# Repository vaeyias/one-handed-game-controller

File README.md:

![Offical github repo (PCBs are here)] https://github.com/MIT-Assistive-Technology/one-handed-game-controller
# :video_game: **One-Handed Game Controller (Left-Handed)**

## 🛠️ **Tools and Materials**
- 3D Printer
- Soldering Kit
- 1 Arduino Micro 
- 2 Thumb Joysticks (KY-023)
- 16 Two-Pin Buttons
- Electrical Wire Cables
- PLA
- 1 ¾ in machine screws size 2-56
- (optional) Foam tape

## :memo: **Instructions**
1. Download ___ files
2. 3D print ___ files
4. Print PCB
5. Solder
6. Upload code to the Arduino
7. Assemble
8. TO DO

## :mag_right: Problem Statement
**Modern game controllers do not accommodate for one-handed users.**

After a stroke or injury, a person may lose some function in their body. Recreational products for the public are often made with the assumption that a person has full control of their body, which means that after permanent injuries, a person may become limited in their choice of hobbies.

Our codesigner, Susan Bibbins, suffers from chronic pain from fibromyalgia and has limited function in her right hand. She always wanted to play video games; however, modern controllers do not accomodate one-handed users.

Our team aims to develop a comfortable and accessible game controller designed specifically for one-handed users so that our codesigner can finally play video games that she has always wanted to try.

## 🔗 References

## ✍️ Acknowledgements
To be completed

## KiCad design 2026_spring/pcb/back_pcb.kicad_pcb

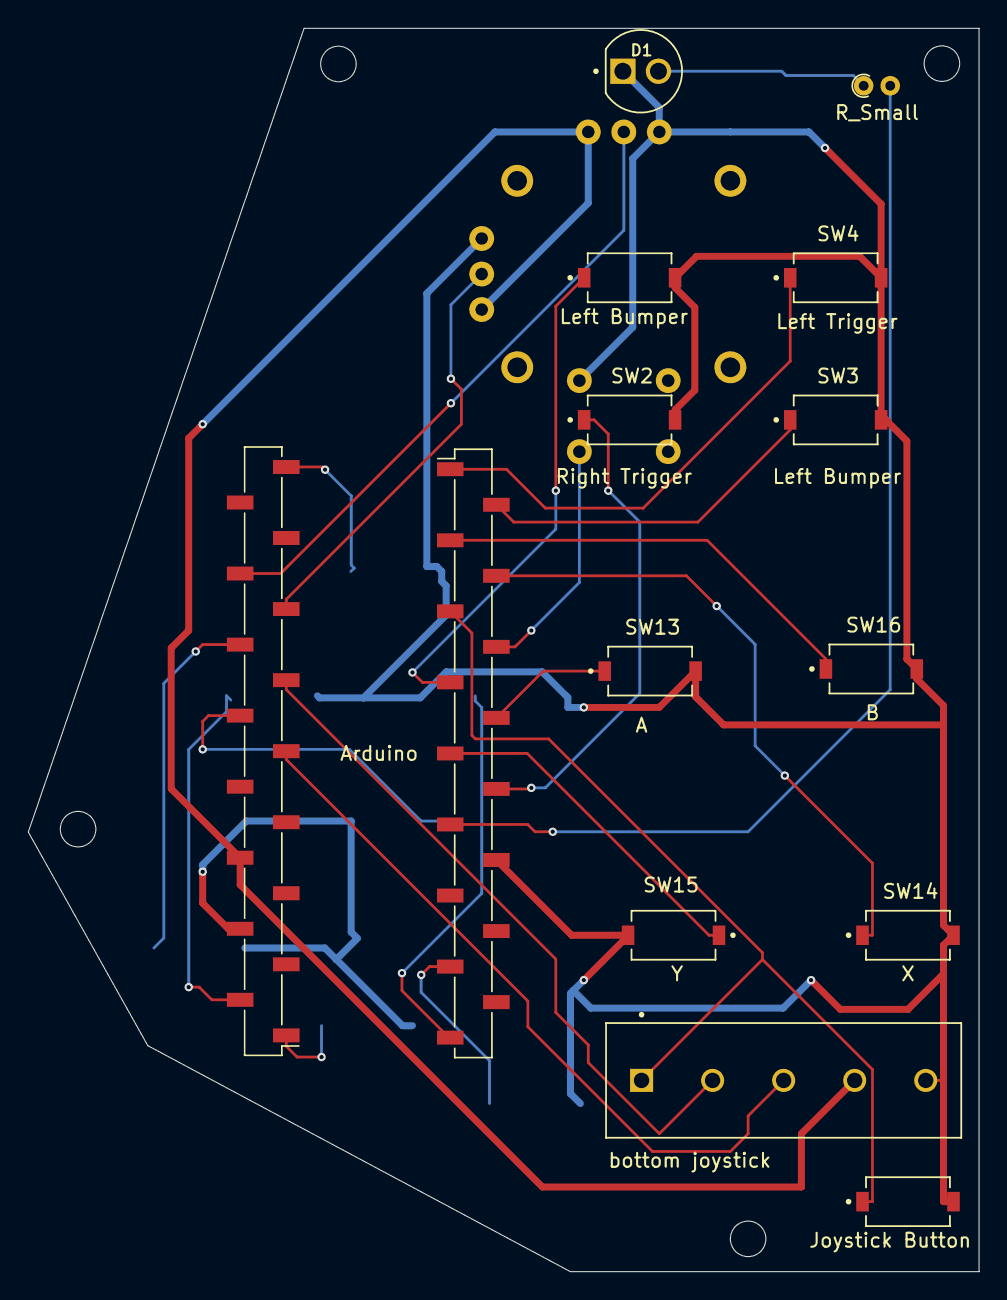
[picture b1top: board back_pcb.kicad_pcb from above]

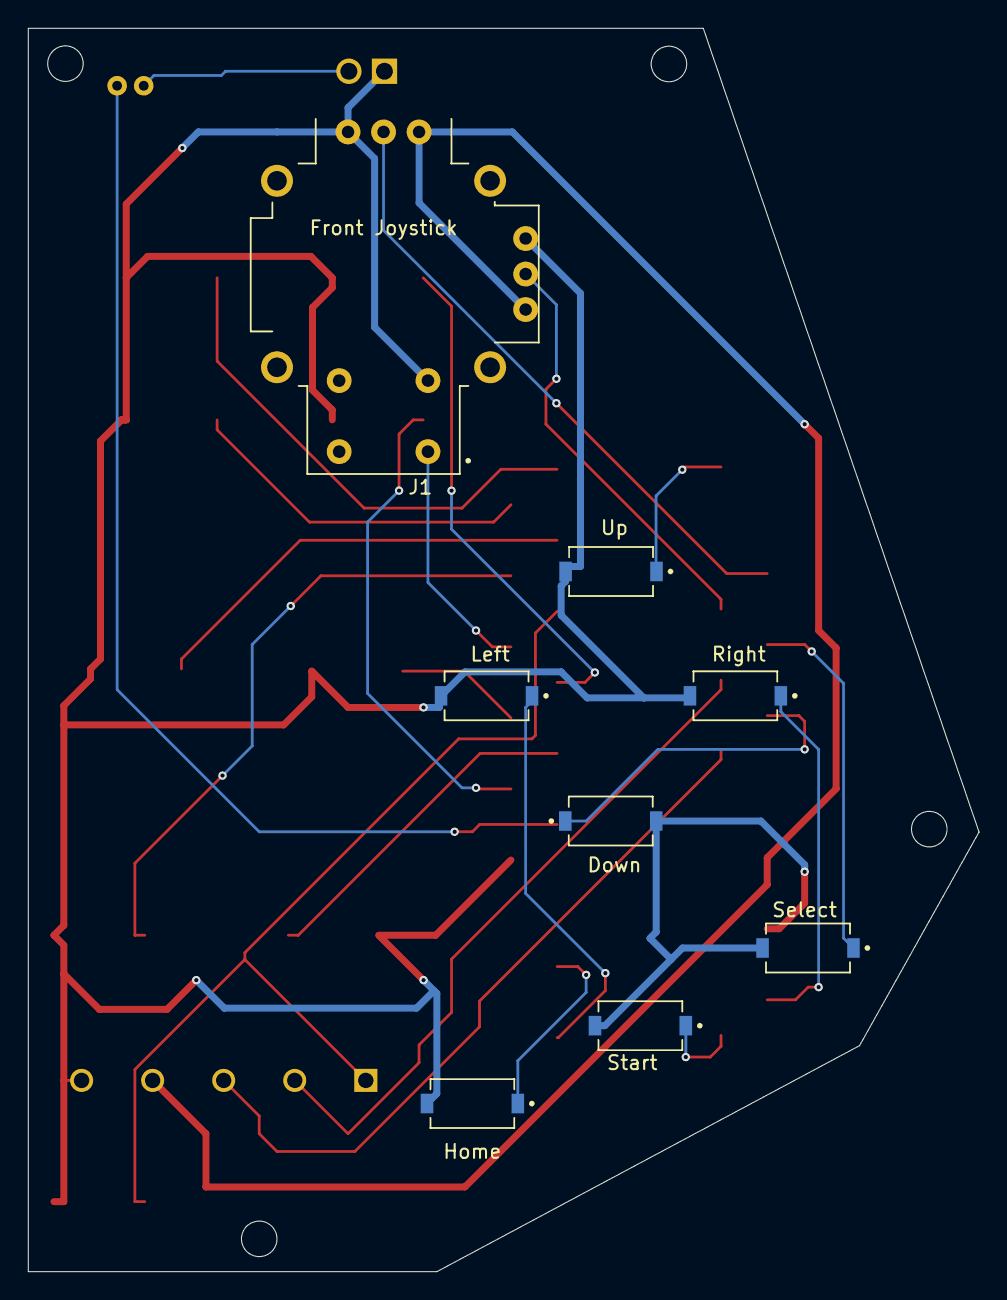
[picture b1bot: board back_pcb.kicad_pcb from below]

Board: 2 copper layers, 68.0 x 88.9 mm, 22 parts (8 on the bottom side), 27 nets.

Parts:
D1: LED; LEDRD254W57D500H1070
J1: Front Joystick; XDCR_COM-09032
J2: bottom joystick; TE_282837-5
J3, J4: Arduino; PinSocket_1x17_P2.54mm_Vertical_SMD_Pin1Left
R1: R_Small; R_Axial_DIN0204_L3.6mm_D1.6mm_P1.90mm_Vertical
SW1: Left Trigger; SW_PTS636_SM43J_SMTR_LFS
SW2: Right Trigger; SW_PTS636_SM43J_SMTR_LFS
SW3, SW4: Left Bumper; SW_PTS636_SM43J_SMTR_LFS
SW5: Up; SW_PTS636_SM43J_SMTR_LFS
SW6: Down; SW_PTS636_SM43J_SMTR_LFS
SW8: Right; SW_PTS636_SM43J_SMTR_LFS
SW9: Left; SW_PTS636_SM43J_SMTR_LFS
SW10: Home; SW_PTS636_SM43J_SMTR_LFS
SW11: Start; SW_PTS636_SM43J_SMTR_LFS
SW13: A; SW_PTS636_SM43J_SMTR_LFS
SW14: X; SW_PTS636_SM43J_SMTR_LFS
SW15: Y; SW_PTS636_SM43J_SMTR_LFS
SW16: B; SW_PTS636_SM43J_SMTR_LFS
SW17: Select; SW_PTS636_SM43J_SMTR_LFS
joy_SW: Joystick Button; SW_PTS636_SM43J_SMTR_LFS

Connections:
/A0: J1.H2, J4.14
/A1: J1.V2, J4.13
/A2: J4.12, SW17.1
/A3: J2.2, J4.11
/A4: J4.10, SW6.1
/A5: J2.3, J4.9
/D1: J3.15, SW10.1
/D2: J3.11, R1.2
/D3: J3.10, SW2.1
/D4: J3.9, SW15.1
/D5: J3.8, SW13.1
/D6: J3.7, SW1.1
/D7: J1.B1A, J3.6
/D8: J2.1, J3.5, joy_SW.1
/D9: J3.4, SW14.1
/D10: J3.3, SW16.1
/D11: J3.2, SW3.1
/D12: J3.1, SW4.1
/D13: J4.17, SW5.1
/D14: J4.2, SW8.1
/D15: J4.1, SW11.1
/D16: J3.17, SW9.1
/GND: D1.GND, J1.B2A, J1.H3, J1.V3, J2.5, J3.12, J4.4, SW1.2, SW2.2, SW3.2, SW4.2, SW5.2, SW6.2, SW8.2, SW9.2, SW10.2, SW11.2, SW13.2, SW14.2, SW15.2, SW16.2, SW17.2, joy_SW.2
/NC: J4.7, J4.8
/R1: D1.R1, R1.1
/RST: J3.13, J4.5
/VCC: J1.H1, J1.V1, J2.4, J4.6

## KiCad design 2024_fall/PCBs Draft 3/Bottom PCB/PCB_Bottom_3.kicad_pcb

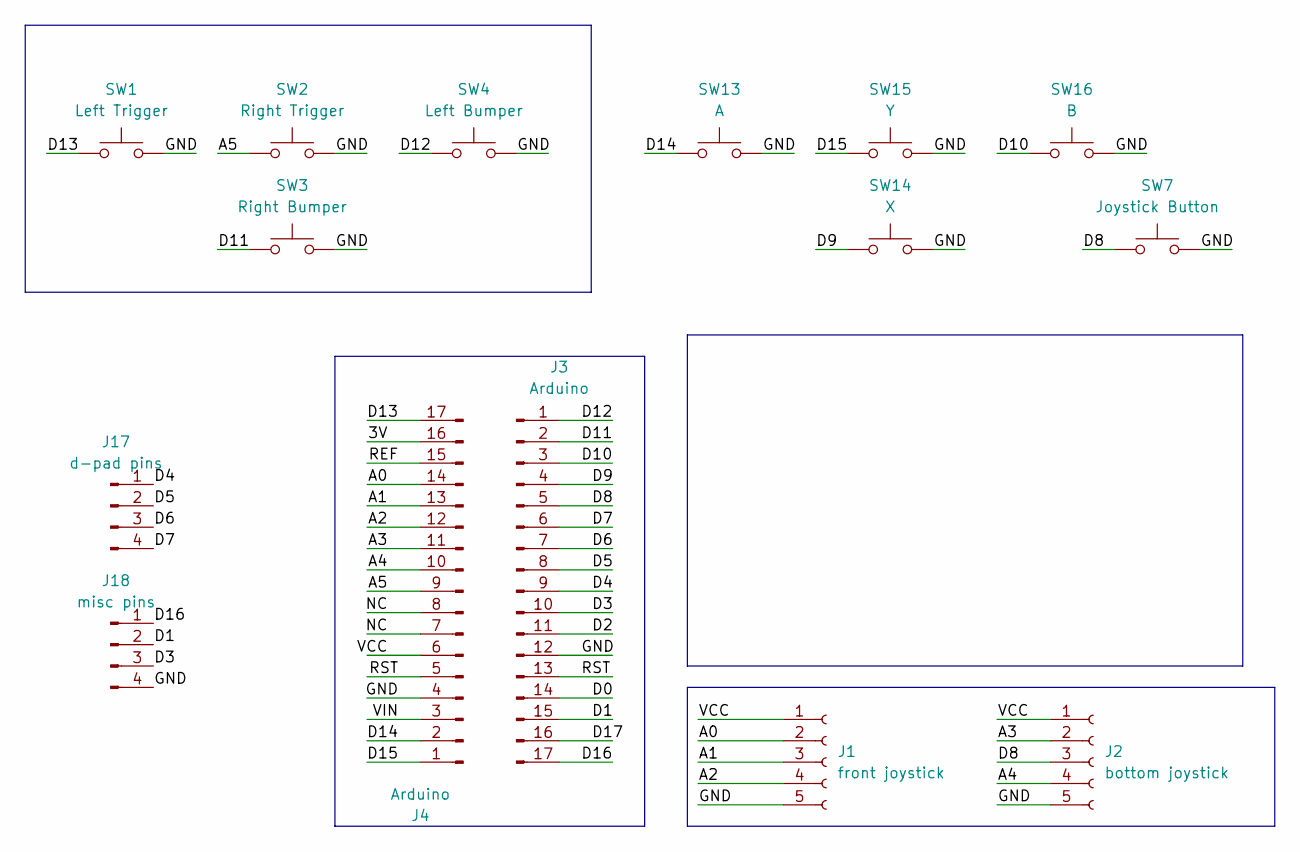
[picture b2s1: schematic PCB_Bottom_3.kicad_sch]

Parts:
J1: front joystick; PinSocket_1x05_P2.54mm_Vertical
J2: bottom joystick; PinSocket_1x05_P2.54mm_Vertical
J3, J4: Arduino; PinSocket_1x17_P2.54mm_Vertical
J17: d-pad pins; PinSocket_1x04_P2.54mm_Vertical
J18: misc pins; PinSocket_1x04_P2.54mm_Vertical
SW1: Left Trigger; SW_BUTT-2
SW2: Right Trigger; SW_BUTT-2
SW3: Right Bumper; SW_BUTT-2
SW4: Left Bumper; SW_BUTT-2
SW7: Joystick Button; SW_BUTT-2
SW13: A; SW_BUTT-2
SW14: X; SW_BUTT-2
SW15: Y; SW_BUTT-2
SW16: B; SW_BUTT-2

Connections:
/3V: J4.16
/A0: J1.2, J4.14
/A1: J1.3, J4.13
/A2: J1.4, J4.12
/A3: J2.2, J4.11
/A4: J2.4, J4.10
/A5: J4.9, SW2.1
/D0: J3.14
/D1: J3.15, J18.2
/D2: J3.11
/D3: J3.10, J18.3
/D4: J3.9, J17.1
/D5: J3.8, J17.2
/D6: J3.7, J17.3
/D7: J3.6, J17.4
/D8: J2.3, J3.5, SW7.1
/D9: J3.4, SW14.1
/D10: J3.3, SW16.1
/D11: J3.2, SW3.1
/D12: J3.1, SW4.1
/D13: J4.17, SW1.1
/D14: J4.2, SW13.1
/D15: J4.1, SW15.1
/D16: J3.17, J18.1
/D17: J3.16
/GND: J1.5, J2.5, J3.12, J4.4, J18.4, SW1.2, SW2.2, SW3.2, SW4.2, SW7.2, SW13.2, SW14.2, SW15.2, SW16.2
/NC: J4.7, J4.8
/REF: J4.15
/RST: J3.13, J4.5
/VCC: J1.1, J2.1, J4.6
/VIN: J4.3

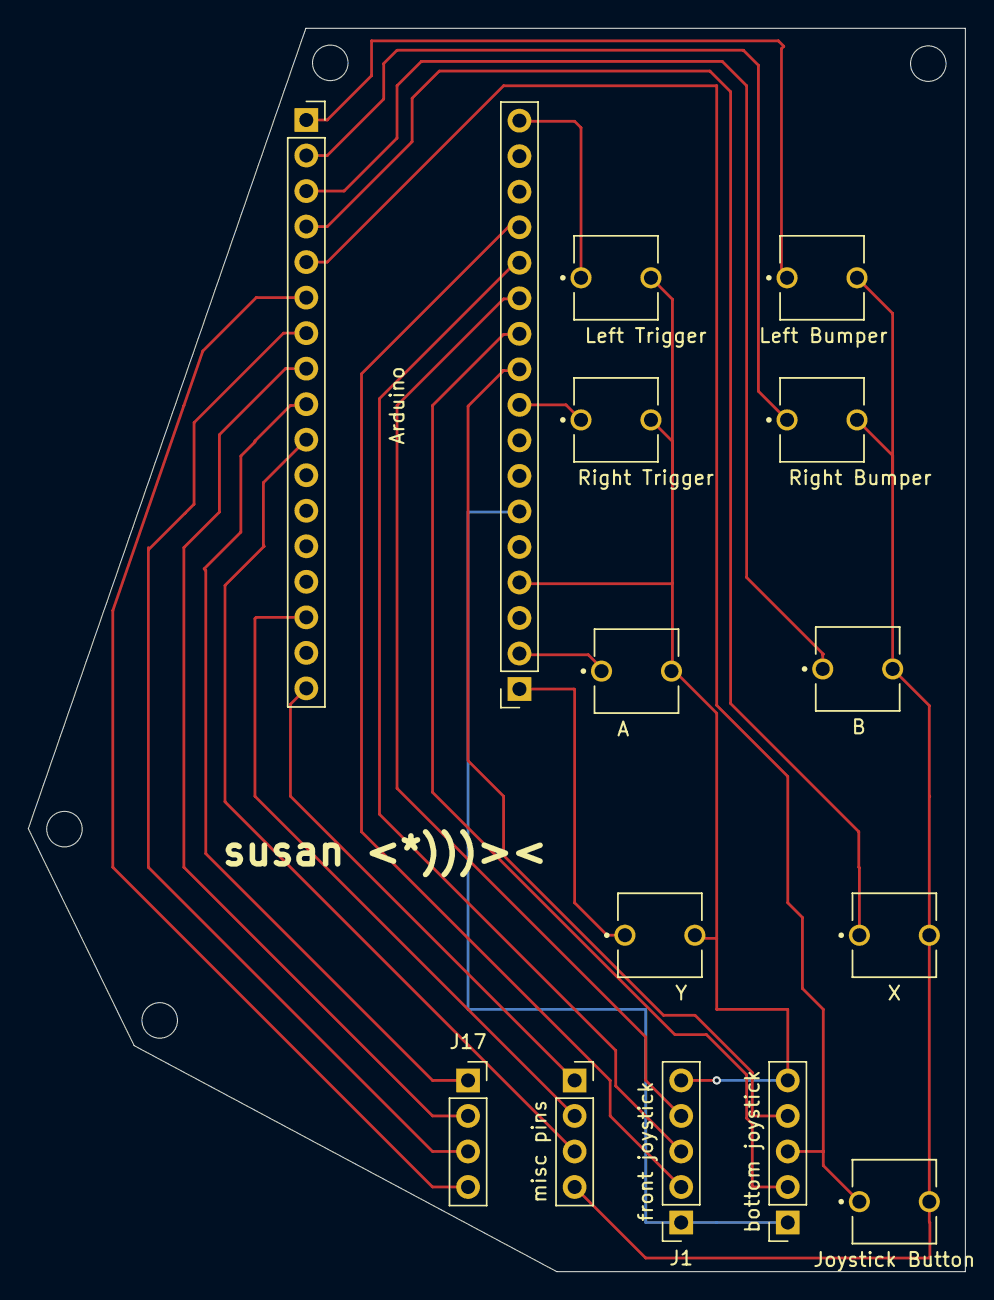
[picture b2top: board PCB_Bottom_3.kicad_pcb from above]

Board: 2 copper layers, 67.0 x 88.9 mm, 15 parts (0 on the bottom side), 25 nets.

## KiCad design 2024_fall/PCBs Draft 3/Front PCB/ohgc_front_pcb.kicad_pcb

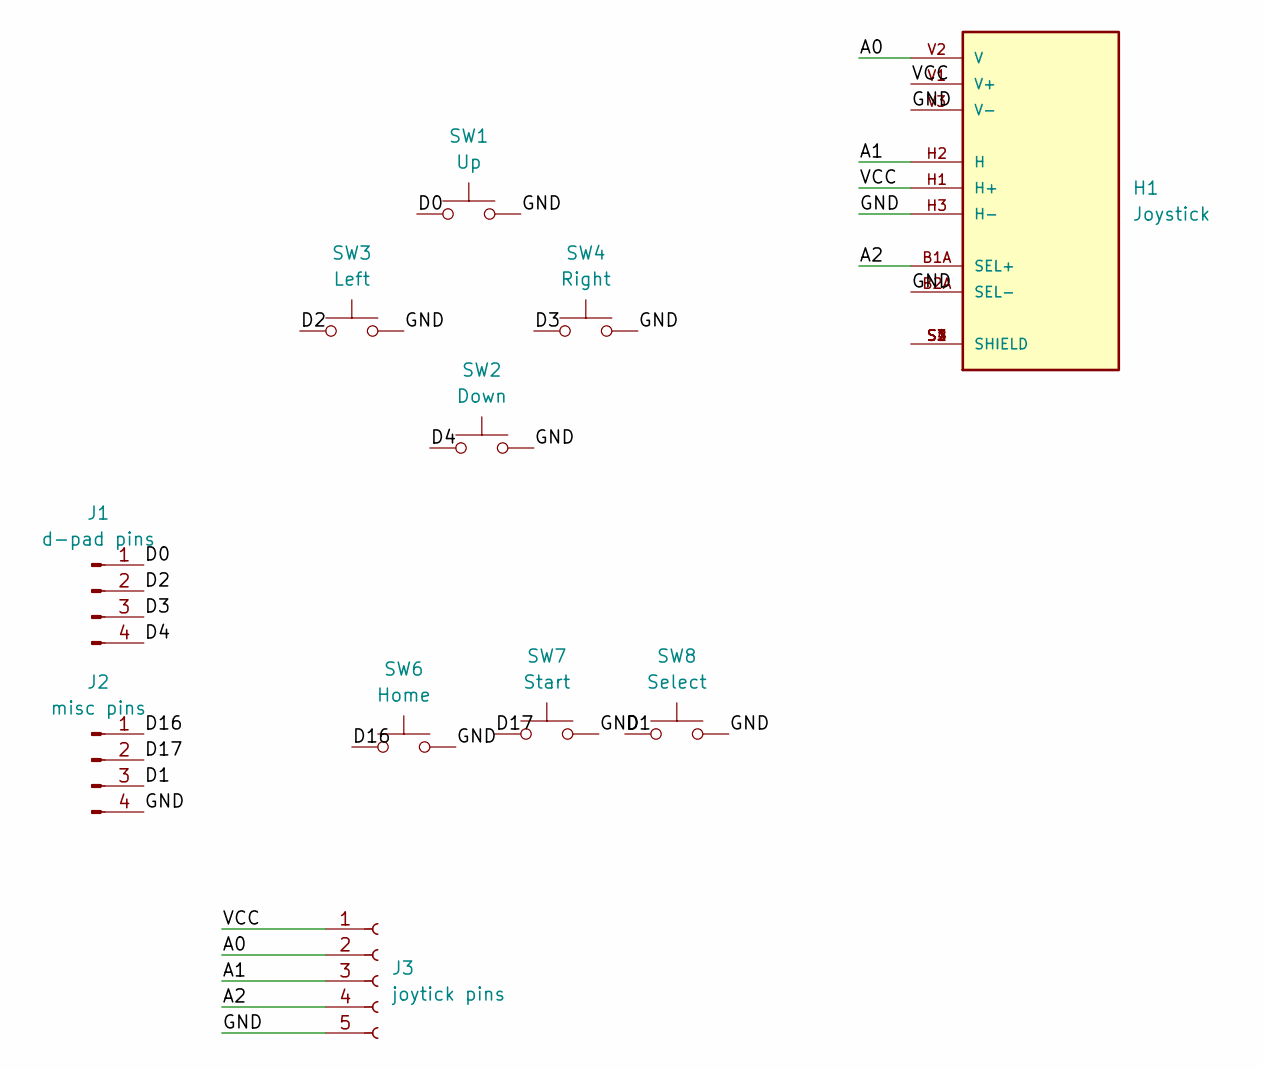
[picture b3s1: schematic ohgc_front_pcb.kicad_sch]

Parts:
H1: Joystick; XDCR_COM-09032; PARTREV N/A
J1: d-pad pins; PinSocket_1x04_P2.54mm_Vertical
J2: misc pins; PinSocket_1x04_P2.54mm_Vertical
J3: joytick pins; PinSocket_1x05_P2.54mm_Vertical
SW1: Up; SW_BUTT-2
SW2: Down; SW_BUTT-2
SW3: Left; SW_BUTT-2
SW4: Right; SW_BUTT-2
SW6: Home; SW_BUTT-2
SW7: Start; SW_BUTT-2
SW8: Select; SW_BUTT-2

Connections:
/A0: H1.V2 (V), J3.2
/A1: H1.H2 (H), J3.3
/A2: H1.B1A (SEL+), J3.4
/D0: J1.1, SW1.1
/D1: J2.3, SW8.1
/D2: J1.2, SW3.1
/D3: J1.3, SW4.1
/D4: J1.4, SW2.1
/D16: J2.1, SW6.1
/D17: J2.2, SW7.1
/GND: H1.B2A (SEL-), H1.H3 (H-), H1.V3 (V-), J2.4, J3.5, SW1.2, SW2.2, SW3.2, SW4.2, SW6.2, SW7.2, SW8.2
/VCC: H1.H1 (H+), H1.V1 (V+), J3.1
unnamed: H1.S1 (SHIELD), H1.S2 (SHIELD), H1.S3 (SHIELD), H1.S4 (SHIELD)

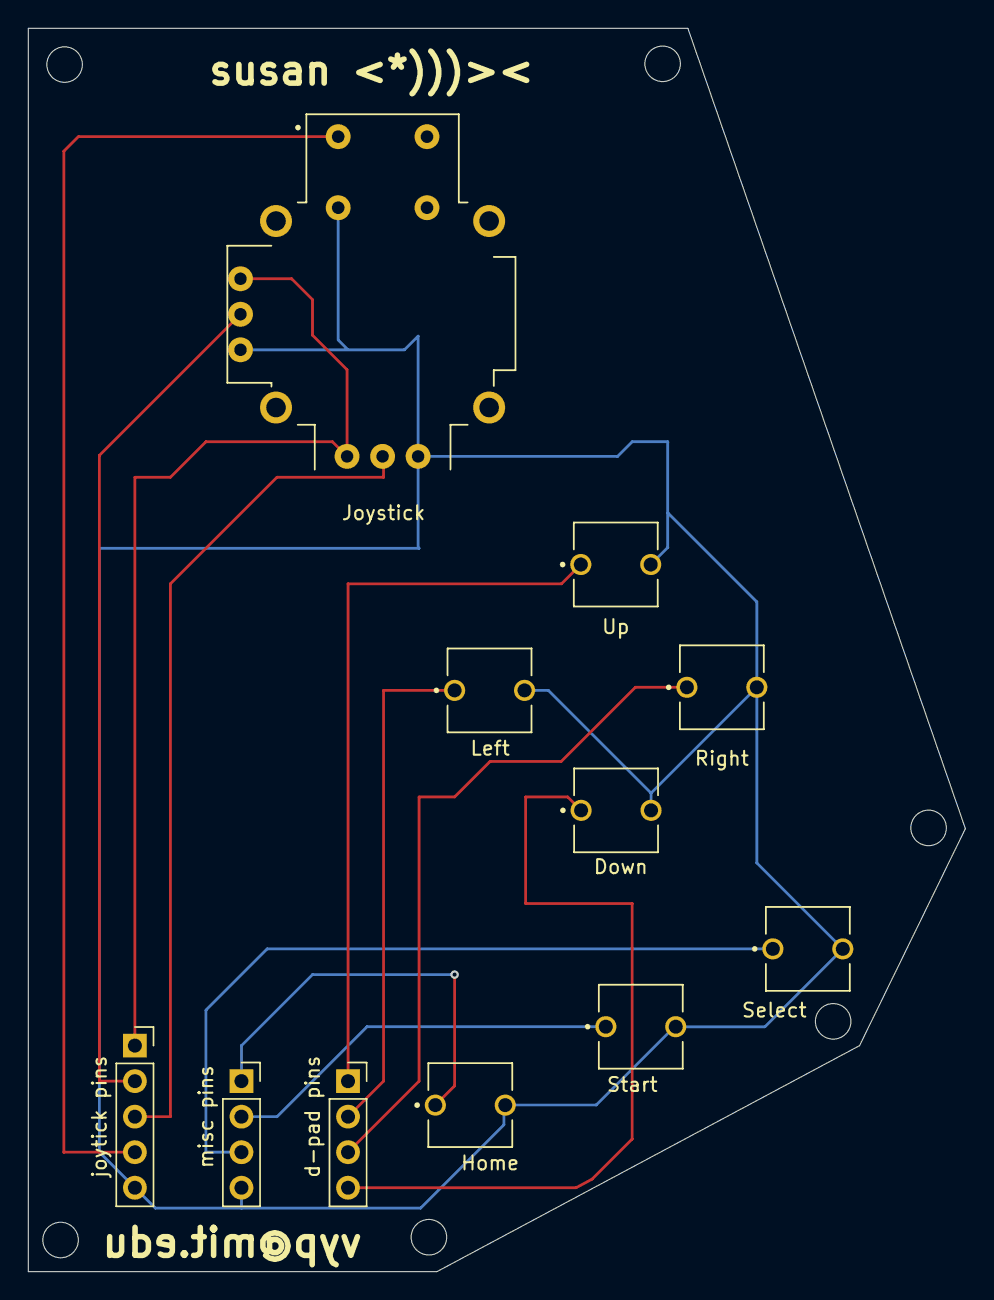
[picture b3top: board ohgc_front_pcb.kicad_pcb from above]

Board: 2 copper layers, 67.0 x 88.9 mm, 11 parts (0 on the bottom side), 13 nets.

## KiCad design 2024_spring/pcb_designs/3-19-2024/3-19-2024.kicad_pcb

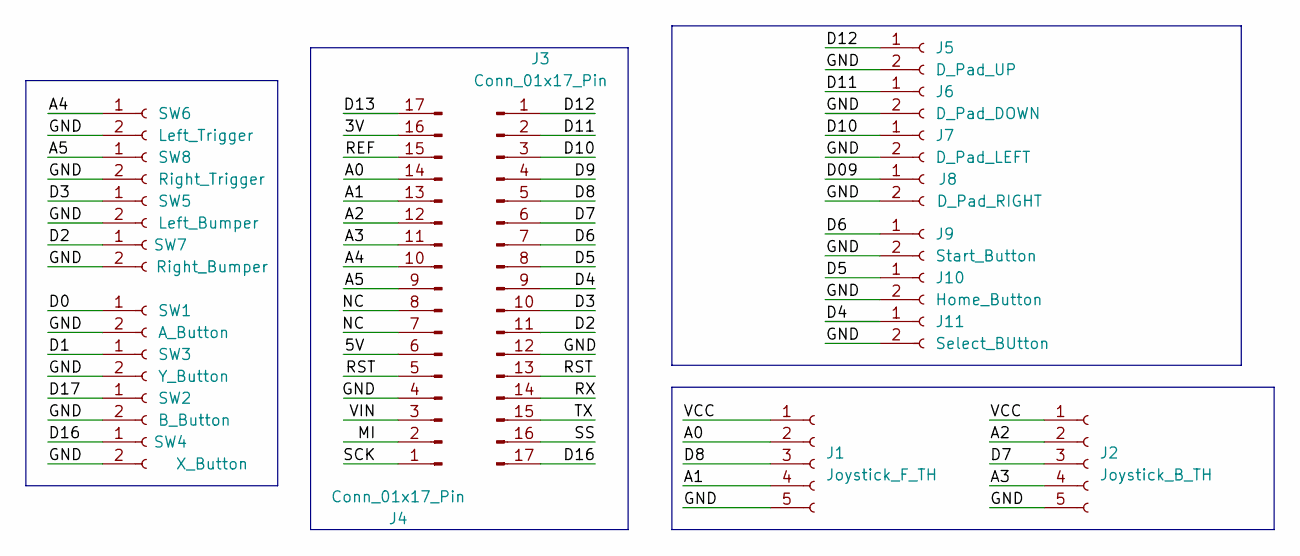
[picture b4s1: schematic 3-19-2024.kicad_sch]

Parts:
J1: Joystick_F_TH; SolderWire-0.1sqmm_1x05_P3.6mm_D0.4mm_OD1mm
J2: Joystick_B_TH; SolderWire-0.1sqmm_1x05_P3.6mm_D0.4mm_OD1mm
J3, J4: Conn_01x17_Pin; PinSocket_1x17_P2.54mm_Vertical
J5: D_Pad_UP; SolderWire-0.1sqmm_1x02_P3.6mm_D0.4mm_OD1mm
J6: D_Pad_DOWN; SolderWire-0.1sqmm_1x02_P3.6mm_D0.4mm_OD1mm
J7: D_Pad_LEFT; SolderWire-0.1sqmm_1x02_P3.6mm_D0.4mm_OD1mm
J8: D_Pad_RIGHT; SolderWire-0.1sqmm_1x02_P3.6mm_D0.4mm_OD1mm
J9: Start_Button; SolderWire-0.1sqmm_1x02_P3.6mm_D0.4mm_OD1mm
J10: Home_Button; SolderWire-0.1sqmm_1x02_P3.6mm_D0.4mm_OD1mm
J11: Select_BUtton; SolderWire-0.1sqmm_1x02_P3.6mm_D0.4mm_OD1mm
SW1: A_Button; SolderWire-0.1sqmm_1x02_P3.6mm_D0.4mm_OD1mm
SW2: B_Button; SolderWire-0.1sqmm_1x02_P3.6mm_D0.4mm_OD1mm
SW3: Y_Button; SolderWire-0.1sqmm_1x02_P3.6mm_D0.4mm_OD1mm
SW4: X_Button; SolderWire-0.1sqmm_1x02_P3.6mm_D0.4mm_OD1mm
SW5: Left_Bumper; SolderWire-0.1sqmm_1x02_P3.6mm_D0.4mm_OD1mm
SW6: Left_Trigger; SolderWire-0.1sqmm_1x02_P3.6mm_D0.4mm_OD1mm
SW7: Right_Bumper; SolderWire-0.1sqmm_1x02_P3.6mm_D0.4mm_OD1mm
SW8: Right_Trigger; SolderWire-0.1sqmm_1x02_P3.6mm_D0.4mm_OD1mm

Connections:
/3V: J4.16
/5V: J4.6
/A0: J1.2, J4.14
/A1: J1.4, J4.13
/A2: J2.2, J4.12
/A3: J2.4, J4.11
/A4: J4.10, SW6.1
/A5: J4.9, SW8.1
/D0: SW1.1
/D1: SW3.1
/D2: J3.11, SW7.1
/D3: J3.10, SW5.1
/D4: J3.9, J11.1
/D5: J3.8, J10.1
/D6: J3.7, J9.1
/D7: J2.3, J3.6
/D8: J1.3, J3.5
/D9: J3.4
/D09: J8.1
/D10: J3.3, J7.1
/D11: J3.2, J6.1
/D12: J3.1, J5.1
/D13: J4.17
/D16: J3.17, SW4.1
/D17: SW2.1
/GND: J1.5, J2.5, J3.12, J4.4, J5.2, J6.2, J7.2, J8.2, J9.2, J10.2, J11.2, SW1.2, SW2.2, SW3.2, SW4.2, SW5.2, SW6.2, SW7.2, SW8.2
/MI: J4.2
/NC: J4.7, J4.8
/REF: J4.15
/RST: J3.13, J4.5
/RX: J3.14
/SCK: J4.1
/SS: J3.16
/TX: J3.15
/VCC: J1.1, J2.1
/VIN: J4.3

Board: 2 copper layers, 19 parts (0 on the bottom side), 21 nets, no tracks yet.

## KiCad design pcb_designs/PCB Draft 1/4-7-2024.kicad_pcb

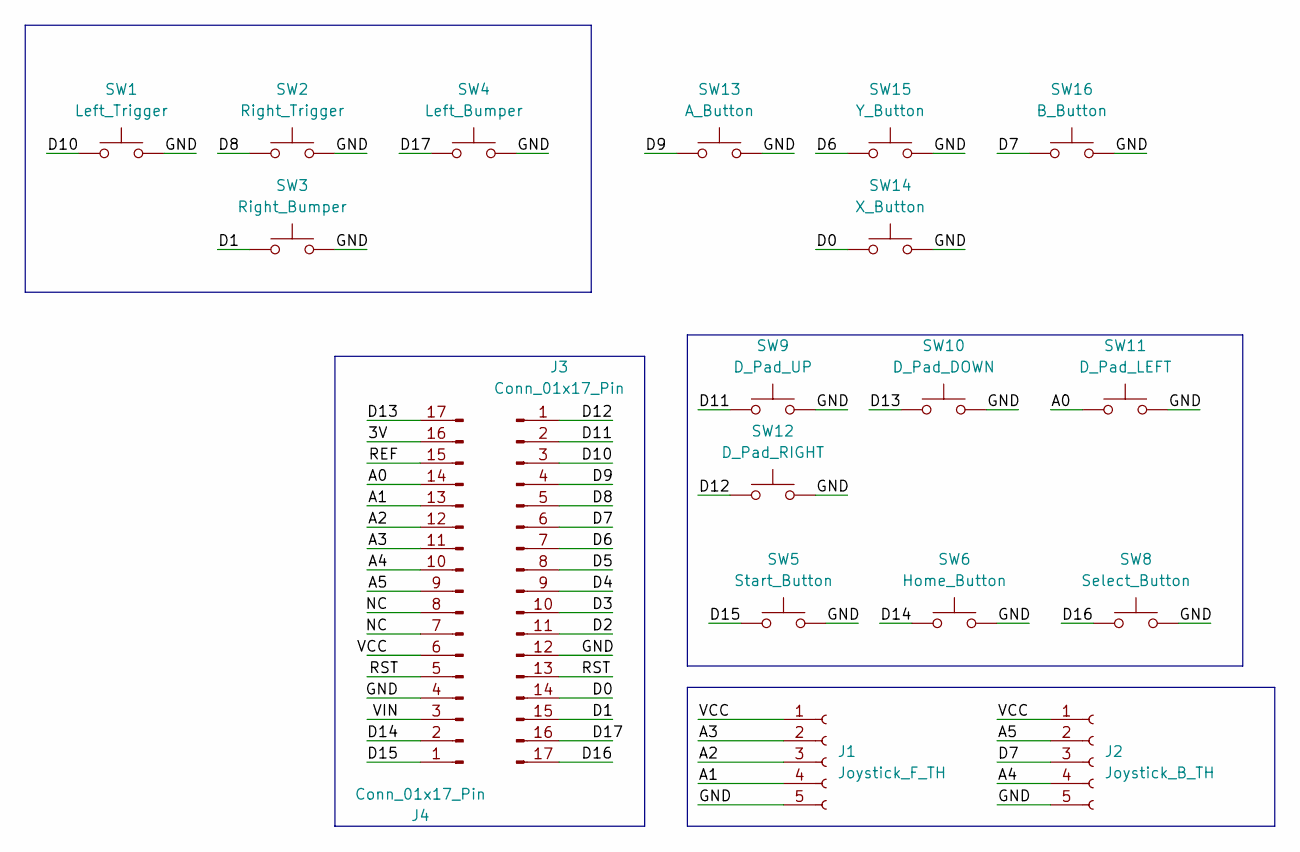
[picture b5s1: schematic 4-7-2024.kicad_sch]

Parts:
J1: Joystick_F_TH; PinSocket_1x05_P2.54mm_Vertical
J2: Joystick_B_TH; PinSocket_1x05_P2.54mm_Vertical
J3, J4: Conn_01x17_Pin; PinSocket_1x17_P2.54mm_Vertical
SW1: Left_Trigger; SW_BUTT-2
SW2: Right_Trigger; SW_BUTT-2
SW3: Right_Bumper; SW_BUTT-2
SW4: Left_Bumper; SW_BUTT-2
SW5: Start_Button; SW_BUTT-2
SW6: Home_Button; SW_BUTT-2
SW8: Select_Button; SW_BUTT-2
SW9: D_Pad_UP; SW_BUTT-2
SW10: D_Pad_DOWN; SW_BUTT-2
SW11: D_Pad_LEFT; SW_BUTT-2
SW12: D_Pad_RIGHT; SW_BUTT-2
SW13: A_Button; SW_BUTT-2
SW14: X_Button; SW_BUTT-2
SW15: Y_Button; SW_BUTT-2
SW16: B_Button; SW_BUTT-2

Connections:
/3V: J4.16
/A0: J4.14, SW11.1
/A1: J1.4, J4.13
/A2: J1.3, J4.12
/A3: J1.2, J4.11
/A4: J2.4, J4.10
/A5: J2.2, J4.9
/D0: J3.14, SW14.1
/D1: J3.15, SW3.1
/D2: J3.11
/D3: J3.10
/D4: J3.9
/D5: J3.8
/D6: J3.7, SW15.1
/D7: J2.3, J3.6, SW16.1
/D8: J3.5, SW2.1
/D9: J3.4, SW13.1
/D10: J3.3, SW1.1
/D11: J3.2, SW9.1
/D12: J3.1, SW12.1
/D13: J4.17, SW10.1
/D14: J4.2, SW6.1
/D15: J4.1, SW5.1
/D16: J3.17, SW8.1
/D17: J3.16, SW4.1
/GND: J1.5, J2.5, J3.12, J4.4, SW1.2, SW2.2, SW3.2, SW4.2, SW5.2, SW6.2, SW8.2, SW9.2, SW10.2, SW11.2, SW12.2, SW13.2, SW14.2, SW15.2, SW16.2
/NC: J4.7, J4.8
/REF: J4.15
/RST: J3.13, J4.5
/VCC: J1.1, J2.1, J4.6
/VIN: J4.3

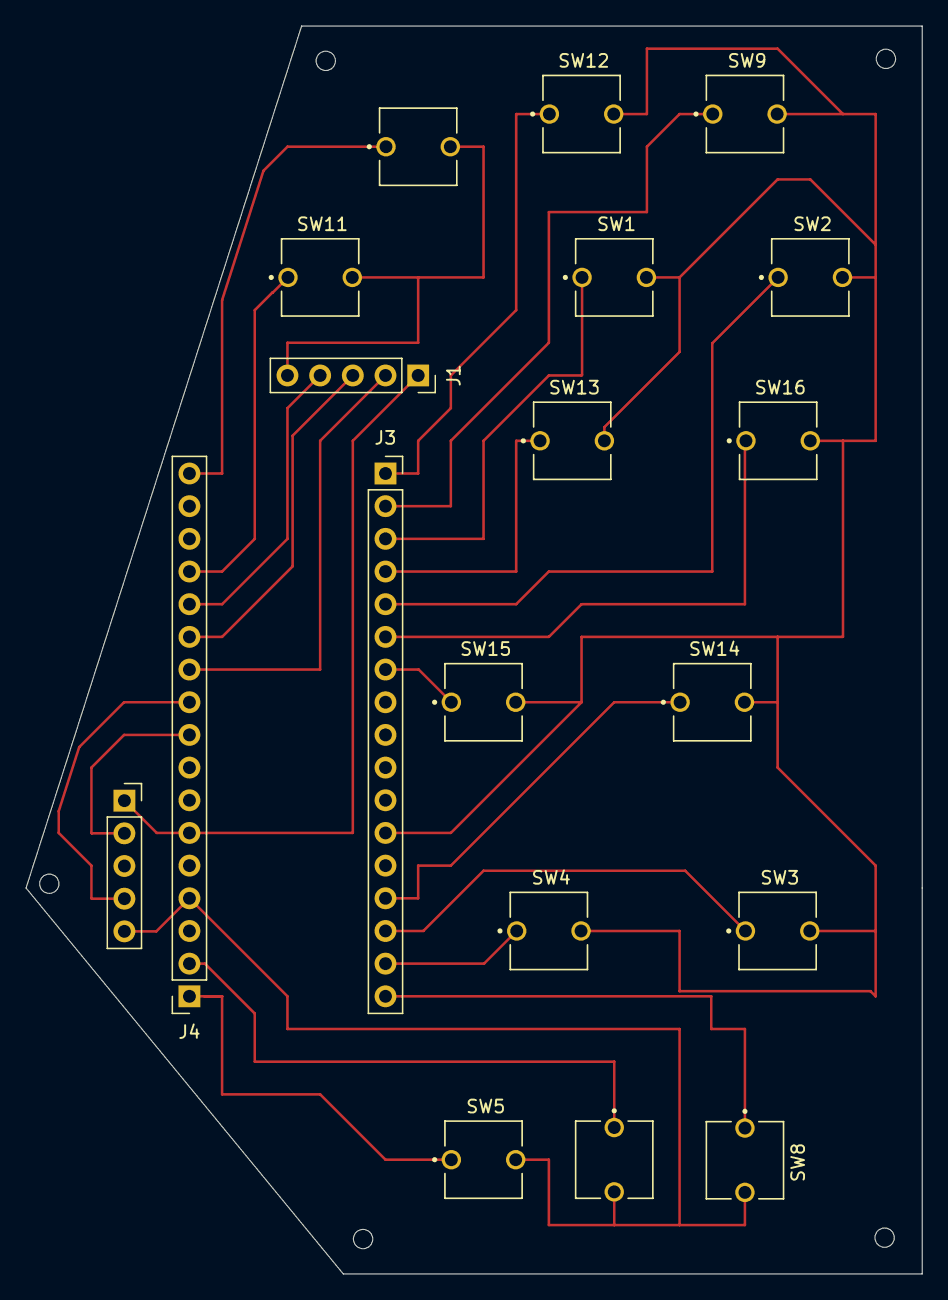
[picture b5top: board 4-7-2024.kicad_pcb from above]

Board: 2 copper layers, 69.7 x 97.0 mm, 19 parts (0 on the bottom side), 24 nets.

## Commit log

2024-02-22 :memo: create readme structure
2024-02-22 :truck: add fall23 solidworks
2024-02-22 :pencil2: fix typo
2024-03-10 :construction: add initial pcb sch
2024-03-10 Added updated PCB Layout and SCH
2024-03-18 3-18-24 🚧
    Updated PCB Schematic and PCB
2024-03-19 🚧 3-19-2024
2024-03-25 :construction: finish draft 1 of wiring
    - changed symbols to two-prong buttons
    - finished initial draft of wiring
2024-04-07 rewire wires to not cross
2024-04-07 :construction: rewire ground connection
2024-04-08 :sparkles: finish first pcb draft
2024-04-29 :sparkles: finish pcb draft 2
2024-04-29 :truck: pcb order 2 zip file
2024-05-13 update pcb draft 2 files
2024-05-13 remove old pcb draft 2 files
2024-05-25 🚗 Bottom Mount
2024-09-22 📝 add instructions section to readme
2024-09-22 :truck: move spring 2024 files to folder
2024-09-22 :memo: update readme
2024-09-22 :sparkles: create fall 2024 folder
2024-10-06 :memo: update readme with materials
2024-10-06 :memo: fix heading sizing
2024-10-07 Create OHGC_v2
2024-10-07 Create READ ME
2024-10-18 Bottom Joystick Holders
2024-10-25 Add files via upload
    Adjusted button positioning to fit on a PCB. Fixed palm rest fillet and added team name engraving.
2024-10-25 Rename OHGC FRONT_SIDE_FINAL.SLDPRT to OHGC FRONT_SIDEv2.1_W_HANDLEHOLE.SLDPRT
2024-10-25 Rename OHGC_BOTTOM_SIDE_FINAL.SLDPRT to OHGC_BOTTOM_SIDEv2.1_W_HANDLEHOLE.SLDPRT
2024-10-27 Create x
2024-10-30 :sparkles: Add PCB Draft 3
    - front pcb
    - modify bottom pcb for front pcb
2024-11-02 :sparkles: updated pcbs for new joysticks
2024-11-02 :sparkles: pcb sketches
2024-11-03 :construction: remove joystick from front pcb
2024-11-14 Create Mount
    A space for Mounts
2024-11-17 :sparkles: fix dpad placement and add missing via
2024-11-24 Rename B_Back_Mount_v3.SLDPRT to B_Back_Mount_v3.SLDPRT
2024-11-24 Rename B_Front_Mount_v3.SLDPRT to B_Front_Mount_v3.SLDPRT
2024-11-24 Rename F_Back_Mount_v3.SLDPRT to F_Back_Mount_v3.SLDPRT
2024-11-24 Rename F_Front_Mount_v3.SLDPRT to F_Front_Mount_v3.SLDPRT
2024-11-24 Rename 2024_fall/bottom_mount.v2.SLDPRT to 2024_fall/MountsV1/bottom_mount.v2.SLDPRT
2024-11-24 Rename 2024_fall/MountPrint1.SLDPRT to 2024_fall/MountsV1/MountPrint1.SLDPRT
2024-11-24 Rename 2024_fall/bottom_mount.v1.SLDPRT to 2024_fall/MountsV1/bottom_mount.v1.SLDPRT
2024-12-05 Create Buttons_Updated
2024-12-06 Create PlayButton
2024-12-22 Create something
2024-12-22 Rename Dpadbutton.v1 (1).SLDPRT to ButtonsV1
2024-12-22 Buttonsv1
2024-12-22 Rename 2024_fall/MountsV1/MountPrint1.SLDPRT to 2024_fall/OHGC_v1/Mounts/MountPrint1.SLDPRT
2024-12-22 Rename 2024_fall/MountsV1/bottom_mount.v1.SLDPRT to 2024_fall/OHGC_v1/Mounts/bottom_mount.v1.SLDPRT
2024-12-22 Rename 2024_fall/MountsV1/bottom_mount.v2.SLDPRT to 2024_fall/OHGC_v1/Mounts/bottom_mount.v2.SLDPRT
2024-12-22 Rename 2024_fall/OHGC_v1/DPadButtonsV1.SLDPRT to 2024_fall/OHGC_v1/Buttons/DPadButtonsV1.SLDPRT
2024-12-22 Rename 2024_fall/OHGC_v1/homebutton.v1 (1) (1).SLDPRT to 2024_fall/OHGC_v1/Buttons/HomeButton_v1.SLDPRT
2024-12-22 Rename DPadButtonsV1.SLDPRT to DPadButton_v1.SLDPRT
2024-12-22 Rename ovalbutton.v1 (1) (1).SLDPRT to OvalButton_v1.SLDPRT
2024-12-22 Rename playbutton.v1 (1) (1).SLDPRT to PlayButton_v1.SLDPRT
2024-12-22 Rename 2024_fall/OHGC_v1/OvalButton_v1.SLDPRT to 2024_fall/OHGC_v1/Mounts/OvalButton_v1.SLDPRT
2024-12-22 Rename OvalButton_v1.SLDPRT to OvalButton_v1.SLDPRT
2024-12-22 Rename 2024_fall/OHGC_v1/PlayButton_v1.SLDPRT to 2024_fall/OHGC_v1/Buttons/PlayButton_v1.SLDPRT
2024-12-22 Rename selectbutton.v1 (1) (1).SLDPRT to SelectButton_v1.SLDPRT
2024-12-22 Rename 2024_fall/OHGC_v1/SelectButton_v1.SLDPRT to 2024_fall/OHGC_v1/Buttons/SelectButton_v1.SLDPRT
2024-12-22 Rename FinalHandleWithScrews2.SLDPRT to HandleWithScrews2.SLDPRT
2024-12-22 Rename 2024_fall/MountsV3/B_Back_Mount_v3.SLDPRT to 2024_fall/OHGC_v2/Mounts/B_Back_Mount_v3.SLDPRT
2024-12-22 Rename 2024_fall/MountsV3/B_Front_Mount_v3.SLDPRT to 2024_fall/OHGC_v2/Mounts/B_Front_Mount_v3.SLDPRT
2024-12-22 Rename 2024_fall/MountsV3/F_Back_Mount_v3.SLDPRT to 2024_fall/OHGC_v2/Mounts/F_Back_Mount_v3.SLDPRT
2024-12-22 Rename 2024_fall/OHGC_v2/F_Front_Mount_v3.SLDPRT to 2024_fall/OHGC_v2/Mounts/F_Front_Mount_v3.SLDPRT
2024-12-22 Rename README to README
2024-12-22 Rename OHGC FRONT_SIDEv2.2.SLDPRT to OHGC FRONT_SIDEv2.2.SLDPRT
2024-12-22 Rename OHGC FRONTv2.2.SLDPRT to OHGC FRONTv2.2.SLDPRT
2024-12-22 Rename OHGC_BOTTOM_SIDEv2.2.SLDPRT to OHGC_BOTTOM_SIDEv2.2.SLDPRT
2024-12-22 Rename OHGC_BOTTOMv2.2.SLDPRT to OHGC_BOTTOMv2.2.SLDPRT
2024-12-22 Rename 2024_fall/Mounts_v4/B_Back_Mount_v4.SLDPRT to 2024_fall/OHGC_v2.3/Mounts_v4/B_Back_Mount_v4.SLDPRT
2024-12-22 Rename B_Front_Mount_v4.SLDPRT to Mounts_v4B_Front_Mount_v4.SLDPRT
2024-12-22 Rename F_Back_Mount_v4.SLDPRT to Mounts_v4F_Back_Mount_v4.SLDPRT
2024-12-22 Rename 2024_fall/Mounts_v4/F_Front_Mount_v4.SLDPRT to 2024_fall/OHGC_v2.3/Mounts_v4/F_Front_Mount_v4.SLDPRT
2024-12-24 Create OHGC_Open_Source_Files
2024-12-24 Create OHGC-Open-Source-Files
2024-12-24 Update and rename ReadMe to README
2024-12-25 Create OHGC-SLDPRT-Files
2024-12-25 Create RAEDME
2024-12-25 Rename OHGC FRONTv2.2.SLDPRT to OHGC FRONTv2.3.SLDPRT
2024-12-25 Create OHGC-STL-Files
2024-12-30 Rename F_Back_Mount_v4.1.STL to Top-Front Mount.STL
2024-12-30 Rename F_Front_Mount_v4.1.STL to Top-Back Mount.STL
2024-12-30 Rename OHGC_BOTTOMv2.2.STL to Back Face.STL
2024-12-30 Rename Back Face.STL to BackFace.STL
2024-12-30 Rename Top-Back Mount.STL to Top-BackMount.STL
2024-12-30 Rename BackFace.STL to Back_Face.STL
2024-12-30 Rename Top-BackMount.STL to Top-Back_Mount.STL
2024-12-30 Rename Top-Front Mount.STL to Top-Front_Mount.STL
2024-12-30 Rename F_Back_Mount_v4.1.SLDPRT to Top-Front_Mount.SLDPRT
2024-12-30 Rename Top-Front_Mount.SLDPRT to Top-Back_Mount.SLDPRT
2024-12-30 Rename F_Front_Mount_v4.1.SLDPRT to Top-Front_Mount.SLDPRT
2024-12-30 Rename OHGC_BOTTOMv2.2.SLDPRT to Back_Face.SLDPRT
2025-03-12 Rename Front_Back_Mount.STL to Top_Back_Mount.STL
2025-03-12 Rename Front_Back_Mount.SLDPRT to Top_Back_Mount.SLDPRT
2026-02-19 Add link to official GitHub repository in README
2026-03-05 :sparkle: merge front and back pcb
2026-03-05 fix back pcb labels
2026-03-05 Add hi.txt with greeting message
2026-03-08 :construction: fix screw terminals
2026-03-13 Rename Front_Side .SLDPRT to Front_Side.SLDPRT
2026-03-15 :sparkle: move arduino to middle of pcb
2026-03-15 Rename Front_Side (2).SLDPRT to Front_Side.SLDPRT
2026-03-19 add pcb order zip file
2026-04-02 Updated holes on Front and Back Side to match Handle
2026-04-07 Adjusted Handle brass insert hole diameter
2026-04-19 Added holes for brass inserts
2026-04-24 Added Posts for Brass Inserts
2026-04-26 create ohgc code
2026-04-26 Updated Back/Front Sides & Faces
    Increased Back Side holes for posts
    Removed post from Back Side
    Removed screw hole from Front Side
    Increased diameter of Front Face Slots for Screw Head
    Removed holes from Back Face
